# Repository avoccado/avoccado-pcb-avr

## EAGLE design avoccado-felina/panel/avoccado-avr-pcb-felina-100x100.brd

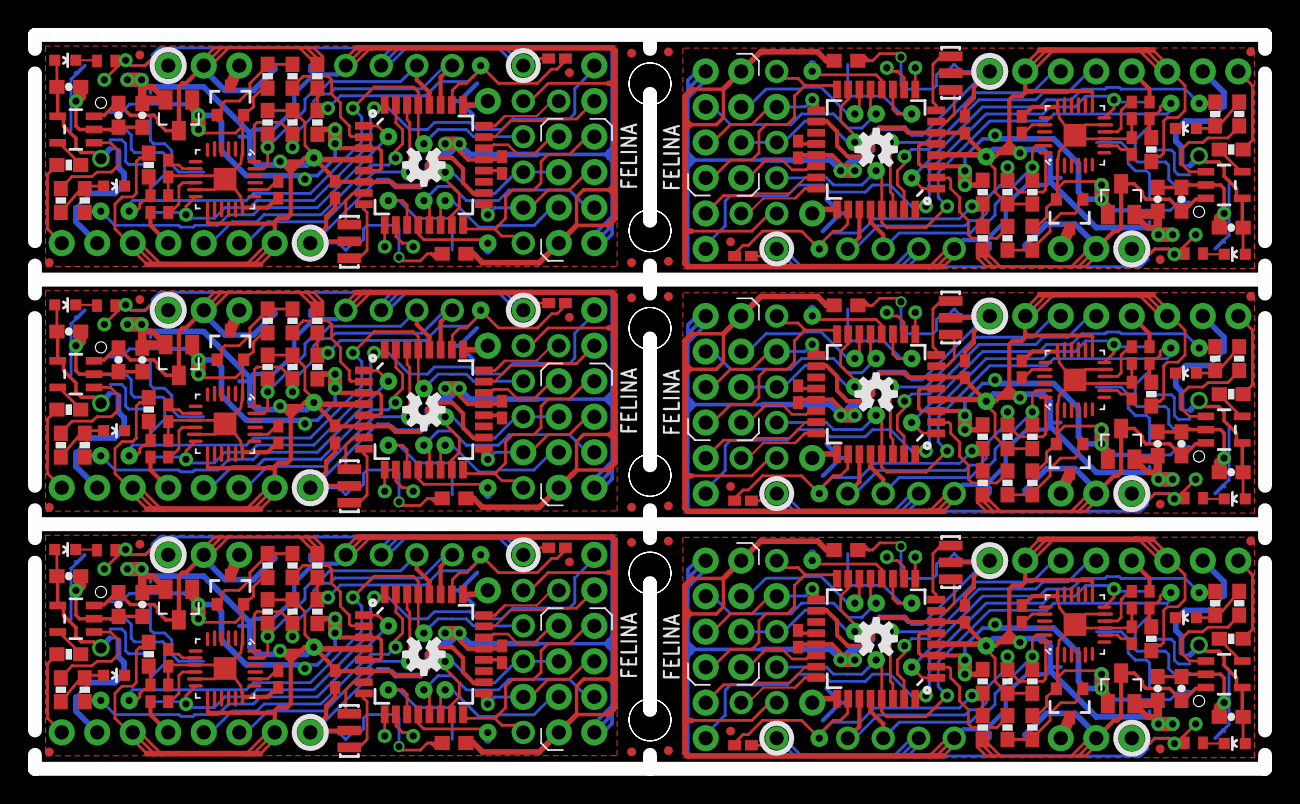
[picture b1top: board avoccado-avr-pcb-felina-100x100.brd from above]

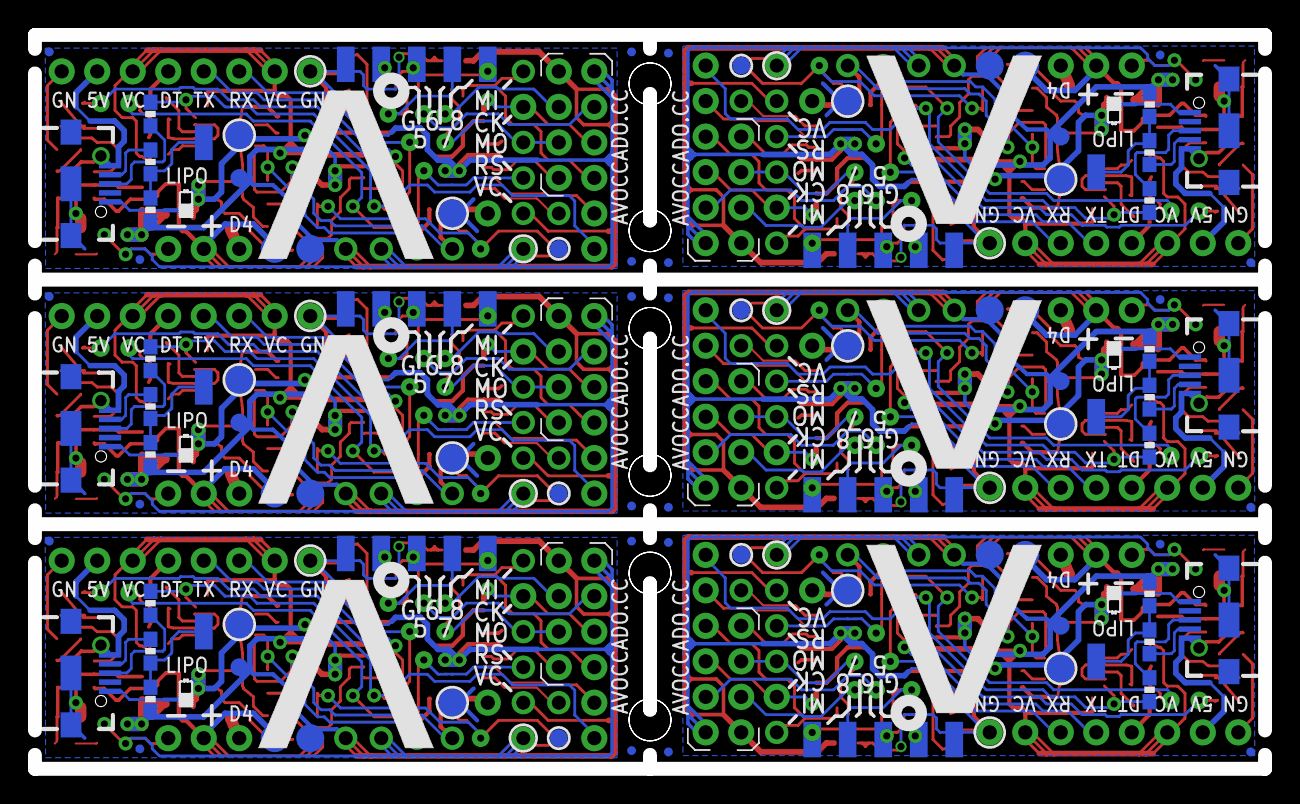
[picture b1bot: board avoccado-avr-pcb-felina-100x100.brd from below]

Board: 2 copper layers, 88.0 x 52.5 mm, 510 parts (120 on the bottom side), 252 nets.

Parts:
C1, C2, C3, C7, C8, C11, C13, C14, C16, C19, C20, C22, C24, C25, C27, C30, C31, C33, C35, C36, C38, C41, C42, C44, C46, C47, C49, C52, C53, C55, C57, C58, C60, C63, C64, C66: 0.1uF; C0402K
C4, C5, C6, C15, C17, C18, C26, C28, C29, C37, C39, C40, C48, C50, C51, C59, C61, C62: 4.7uF; 0603-CAP
C9, C21, C32, C43, C54, C65: 2.2nF; C0402K
C10, C12, C23, C34, C45, C56: 0.1uF; C0603
D1, D2, D3, D4, D5, D6, D7, D8, D9, D10, D11, D12: LED; LED-0603
FID1, FID2, FID3, FID4, FID5, FID6, FID7, FID8, FID9, FID10, FID11, FID12, FID13, FID14, FID15, FID16, FID17, FID18, FID19, FID20, FID21, FID22, FID23, FID24, FID25, FID26, FID27, FID28, FID29, FID30, FID31, FID32, FID33, FID34, FID35, FID36, FID37, FID38, FID39, FID40, FID41, FID42, FID43, FID44, FID45, FID46, FID47, FID48, FID49, FID50, FID51, FID52, FID53, FID54: FIDUCIALUFIDUCIAL; MICRO-FIDUCIAL
JP1, JP4, JP5, JP12, JP14, JP15, JP16, JP20, JP30, JP31, JP35, JP37, JP38, JP43, JP52, JP53, JP54, JP55, JP56, JP57, JP64, JP66, JP67, JP72, JP81, JP82, JP83, JP84, JP85, JP86, JP93, JP95, JP96, JP101, JP110, JP111, JP112, JP113, JP114, JP115, JP122, JP124, JP125, JP130, JP139, JP140, JP141, JP142, JP143, JP144, JP151, JP153, JP154, JP159, JP168, JP169, JP170, JP171, JP172, JP173: M01NOSILK-KIT; 1X01NS-KIT
JP2, JP27, JP28, JP29, JP48, JP49, JP50, JP51, JP77, JP78, JP79, JP80, JP106, JP107, JP108, JP109, JP135, JP136, JP137, JP138, JP164, JP165, JP166, JP167: M021X02_NO_SILK; 1X02_NO_SILK
JP3, JP6, JP7, JP8, JP9, JP10, JP11, JP13, JP17, JP18, JP19, JP21, JP23, JP24, JP25, JP26, JP32, JP33, JP34, JP36, JP39, JP40, JP41, JP42, JP44, JP45, JP46, JP47, JP59, JP60, JP61, JP62, JP63, JP65, JP68, JP69, JP70, JP71, JP73, JP74, JP75, JP76, JP88, JP89, JP90, JP91, JP92, JP94, JP97, JP98, JP99, JP100, JP102, JP103, JP104, JP105, JP117, JP118, JP119, JP120, JP121, JP123, JP126, JP127, JP128, JP129, JP131, JP132, JP133, JP134, JP146, JP147, JP148, JP149, JP150, JP152, JP155, JP156, JP157, JP158, JP160, JP161, JP162, JP163: M01PTH; 1X01
JP22, JP58, JP87, JP116, JP145, JP174: USB_MICROB_PLUGCONN-11752; USB-B-MICRO-SMD_V03
LDO, LDO1, LDO2, LDO3, LDO4, LDO5: MCP1703CB; SOT23
LOGO1, LOGO2, LOGO3, LOGO4, LOGO5, LOGO6: OSHW-LOGOS; OSHW-LOGO-S
MCU, MCU1, MCU2, MCU3, MCU4, MCU5: ATMEGA328P_TQFP; TQFP32-08
Q1, Q3, Q5, Q7, Q9, Q11: 16MHz; RESONATOR-SMD
Q2, Q4, Q6, Q8, Q10, Q12: FET; SOT23-3
R1, R6, R16, R20, R30, R34, R44, R48, R58, R62, R72, R76: 511R; 0603-RES
R2, R10, R11, R12, R23, R24, R29, R37, R38, R43, R51, R52, R57, R65, R66, R71, R79, R80: 10K; 0603-RES
R3, R4, R15, R17, R18, R27, R31, R32, R41, R45, R46, R55, R59, R60, R69, R73, R74, R83: 2K; 0603-RES
R5, R7, R8, R19, R21, R22, R33, R35, R36, R47, R49, R50, R61, R63, R64, R75, R77, R78: 4.7M; 0603-RES
R9, R28, R42, R56, R70, R84: 2K; R0402
R13, R14, R25, R26, R39, R40, R53, R54, R67, R68, R81, R82: 68R; 0603-RES
TP1, TP6, TP7, TP8, TP9, TP11, TP14, TP15, TP16, TP17, TP21, TP23, TP27, TP28, TP29, TP30, TP34, TP36, TP40, TP41, TP42, TP43, TP47, TP49, TP53, TP54, TP55, TP56, TP60, TP62, TP66, TP67, TP68, TP69, TP73, TP75: TEST-POINT2; PAD.02X.02
TP2, TP18, TP31, TP44, TP57, TP70: M01PTH; 1X01
TP3, TP5, TP19, TP20, TP32, TP33, TP45, TP46, TP58, TP59, TP71, TP72: TEST-POINT3X5; PAD.03X.05
TP4, TP10, TP12, TP13, TP22, TP24, TP25, TP26, TP35, TP37, TP38, TP39, TP48, TP50, TP51, TP52, TP61, TP63, TP64, TP65, TP74, TP76, TP77, TP78: TPTP20R; TP20R
U1, U4, U6, U8, U10, U12: MPU-6000QFN-24; QFN-24-TESTING
U2, U3, U5, U7, U9, U11: MCP73831; SOT23-5

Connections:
3.3V1: C12.1, C13.2, C18.1, JP34.1, JP41.1, JP48.2, JP52.1, JP56.1, LDO1.2, MCU1.4, MCU1.6, MCU1.18, R12.2, R23.2, R24.2, R27.2, TP19.P$1, TP25.TP, U4.13
3.3V2: C23.1, C24.2, C29.1, JP63.1, JP70.1, JP77.2, JP81.1, JP85.1, LDO2.2, MCU2.4, MCU2.6, MCU2.18, R29.2, R37.2, R38.2, R41.2, TP32.P$1, TP38.TP, U6.13
3.3V3: C34.1, C35.2, C40.1, JP92.1, JP99.1, JP106.2, JP110.1, JP114.1, LDO3.2, MCU3.4, MCU3.6, MCU3.18, R43.2, R51.2, R52.2, R55.2, TP45.P$1, TP51.TP, U8.13
3.3V4: C45.1, C46.2, C51.1, JP121.1, JP128.1, JP135.2, JP139.1, JP143.1, LDO4.2, MCU4.4, MCU4.6, MCU4.18, R57.2, R65.2, R66.2, R69.2, TP58.P$1, TP64.TP, U10.13
3.3V5: C3.2, C6.1, C10.1, JP1.1, JP2.2, JP4.1, JP11.1, JP18.1, LDO.2, MCU.4, MCU.6, MCU.18, R2.2, R10.2, R11.2, R15.2, TP5.P$1, TP13.TP, U1.13
3.3V6: C56.1, C57.2, C62.1, JP150.1, JP157.1, JP164.2, JP168.1, JP172.1, LDO5.2, MCU5.4, MCU5.6, MCU5.18, R71.2, R79.2, R80.2, R83.2, TP71.P$1, TP77.TP, U12.13
5V1: C15.1, D4.A, JP40.1, JP58.VBUS1, U3.4
5V2: C26.1, D6.A, JP69.1, JP87.VBUS1, U5.4
5V3: C37.1, D8.A, JP98.1, JP116.VBUS1, U7.4
5V4: C48.1, D10.A, JP127.1, JP145.VBUS1, U9.4
5V5: C4.1, D2.A, JP17.1, JP22.VBUS1, U2.4
5V6: C59.1, D12.A, JP156.1, JP174.VBUS1, U11.4
7-TO-D-: R14.1, R15.1, TP11.P$1
7-TO-D-1: R26.1, R27.1, TP23.P$1
7-TO-D-2: R40.1, R41.1, TP36.P$1
7-TO-D-3: R54.1, R55.1, TP49.P$1
7-TO-D-4: R68.1, R69.1, TP62.P$1
7-TO-D-5: R82.1, R83.1, TP75.P$1
A6: JP30.1, MCU.28, R10.1, U1.23
A7: JP54.1, MCU1.28, R23.1, U4.23
A7-NRF-IRQ1: JP51.2, MCU1.22
A7-NRF-IRQ2: JP80.2, MCU2.22
A7-NRF-IRQ3: JP109.2, MCU3.22
A7-NRF-IRQ4: JP138.2, MCU4.22
A7-NRF-IRQ5: JP29.2, MCU.22
A7-NRF-IRQ6: JP167.2, MCU5.22
A8: JP55.1, MCU1.27, R24.1, U4.24
A9: C19.1, MCU1.26, R21.2, R22.1
A10: JP44.1, MCU1.25
A11: JP43.1, MCU1.24
A12: JP42.1, MCU1.23
A14: JP83.1, MCU2.28, R37.1, U6.23
A15: JP84.1, MCU2.27, R38.1, U6.24
A16: C30.1, MCU2.26, R35.2, R36.1
A17: JP73.1, MCU2.25
A18: JP72.1, MCU2.24
A19: JP71.1, MCU2.23
A21: JP112.1, MCU3.28, R51.1, U8.23
A22: JP113.1, MCU3.27, R52.1, U8.24
A23: C41.1, MCU3.26, R49.2, R50.1
A24: JP102.1, MCU3.25
A25: JP101.1, MCU3.24
A26: JP100.1, MCU3.23
A28: JP141.1, MCU4.28, R65.1, U10.23
A29: JP142.1, MCU4.27, R66.1, U10.24
A30: C52.1, MCU4.26, R63.2, R64.1
A31: JP131.1, MCU4.25
A32: JP130.1, MCU4.24
A33: JP129.1, MCU4.23
A35: JP31.1, MCU.27, R11.1, U1.24
A36: C7.1, MCU.26, R7.2, R8.1
A37: JP21.1, MCU.25
A38: JP20.1, MCU.24
A39: JP19.1, MCU.23
A41: JP170.1, MCU5.28, R79.1, U12.23
A42: JP171.1, MCU5.27, R80.1, U12.24
A43: C63.1, MCU5.26, R77.2, R78.1
A44: JP160.1, MCU5.25
A45: JP159.1, MCU5.24
A46: JP158.1, MCU5.23
AREF1: C14.2, MCU1.20
AREF2: C25.2, MCU2.20
AREF3: C36.2, MCU3.20
AREF4: C47.2, MCU4.20
AREF5: C1.2, MCU.20
AREF6: C58.2, MCU5.20
CHG-PROG1: R17.2, U3.5
CHG-PROG2: R31.2, U5.5
CHG-PROG3: R45.2, U7.5
CHG-PROG4: R59.2, U9.5
CHG-PROG5: R3.2, U2.5
CHG-PROG6: R73.2, U11.5
D1: JP49.1, MCU1.13
D2: MCU1.12, TP17.P$1
D2-INT1: MCU1.32, R25.1, TP18.1, U4.12
D2-INT2: MCU2.32, R39.1, TP31.1, U6.12
D2-INT3: MCU3.32, R53.1, TP44.1, U8.12
D2-INT4: MCU4.32, R67.1, TP57.1, U10.12
D2-INT5: MCU.32, R13.1, TP2.1, U1.12
D2-INT6: MCU5.32, R81.1, TP70.1, U12.12
D3: JP27.1, MCU.13
D8: MCU.12, TP8.P$1
D11: MCU1.1, R20.1
D12: MCU1.2, R16.1
D13: MCU1.9, TP14.P$1
D14: MCU1.10, TP15.P$1
D15: MCU1.11, TP16.P$1
D16: JP49.2, MCU1.14
D17: JP78.1, MCU2.13
D18: MCU2.12, TP30.P$1
D19: MCU2.1, R34.1
D20: MCU2.2, R30.1
D21: MCU2.9, TP27.P$1
D22: MCU2.10, TP28.P$1
D23: MCU2.11, TP29.P$1
D24: JP78.2, MCU2.14
D25: JP107.1, MCU3.13
D26: MCU3.12, TP43.P$1
D27: MCU3.1, R48.1
D28: MCU3.2, R44.1
D29: MCU3.9, TP40.P$1
D30: MCU3.10, TP41.P$1
D31: MCU3.11, TP42.P$1
D32: JP107.2, MCU3.14
D33: JP136.1, MCU4.13
D34: MCU4.12, TP56.P$1
D35: MCU4.1, R62.1
D36: MCU4.2, R58.1
D37: MCU4.9, TP53.P$1
D38: MCU4.10, TP54.P$1
D39: MCU4.11, TP55.P$1
D40: JP136.2, MCU4.14
D41: MCU.1, R6.1
D42: MCU.2, R1.1
D43: MCU.9, TP1.P$1
D44: MCU.10, TP6.P$1
D45: MCU.11, TP7.P$1
D46: JP27.2, MCU.14
D47: JP165.1, MCU5.13
D48: MCU5.12, TP69.P$1
D49: MCU5.1, R76.1
D50: MCU5.2, R72.1
D51: MCU5.9, TP66.P$1
D52: MCU5.10, TP67.P$1
D53: MCU5.11, TP68.P$1
D54: JP165.2, MCU5.14
DTR1: C16.2, JP33.1
DTR2: C27.2, JP62.1
DTR3: C38.2, JP91.1
DTR4: C49.2, JP120.1
DTR5: C2.2, JP10.1
DTR6: C60.2, JP149.1
GND: C1.1, C3.1, C4.2, C5.2, C6.2, C7.2, C8.2, C9.2, C10.2, C11.2, D1.C, JP2.1, JP3.1, JP5.1, JP6.1, JP16.1, JP22.GND1, JP22.SHIELD1, JP22.SHIELD2, JP22.SHIELD3, JP25.1, LDO.1, MCU.3, MCU.5, MCU.21, Q1.2, Q2.2, R3.1, R5.1, R7.1, R9.1, TP3.P$1, TP4.TP, TP9.P$1, TP12.TP, U1.1, U1.9, U1.11, U1.18, U2.2
GND1: C12.2, C13.1, C14.1, C15.2, C17.2, C18.2, C19.2, C20.2, C21.2, C22.2, D3.C, JP7.1, JP39.1, JP47.1, JP48.1, JP53.1, JP57.1, JP58.GND1, JP58.SHIELD1, JP58.SHIELD2, JP58.SHIELD3, LDO1.1, MCU1.3, MCU1.5, MCU1.21, Q3.2, Q4.2, R17.1, R19.1, R21.1, R28.1, TP20.P$1, TP21.P$1, TP24.TP, TP26.TP, U3.2, U4.1, U4.9, U4.11, U4.18
GND2: C23.2, C24.1, C25.1, C26.2, C28.2, C29.2, C30.2, C31.2, C32.2, C33.2, D5.C, JP59.1, JP68.1, JP76.1, JP77.1, JP82.1, JP86.1, JP87.GND1, JP87.SHIELD1, JP87.SHIELD2, JP87.SHIELD3, LDO2.1, MCU2.3, MCU2.5, MCU2.21, Q5.2, Q6.2, R31.1, R33.1, R35.1, R42.1, TP33.P$1, TP34.P$1, TP37.TP, TP39.TP, U5.2, U6.1, U6.9, U6.11, U6.18
GND3: C34.2, C35.1, C36.1, C37.2, C39.2, C40.2, C41.2, C42.2, C43.2, C44.2, D7.C, JP88.1, JP97.1, JP105.1, JP106.1, JP111.1, JP115.1, JP116.GND1, JP116.SHIELD1, JP116.SHIELD2, JP116.SHIELD3, LDO3.1, MCU3.3, MCU3.5, MCU3.21, Q7.2, Q8.2, R45.1, R47.1, R49.1, R56.1, TP46.P$1, TP47.P$1, TP50.TP, TP52.TP, U7.2, U8.1, U8.9, U8.11, U8.18
GND4: C45.2, C46.1, C47.1, C48.2, C50.2, C51.2, C52.2, C53.2, C54.2, C55.2, D9.C, JP117.1, JP126.1, JP134.1, JP135.1, JP140.1, JP144.1, JP145.GND1, JP145.SHIELD1, JP145.SHIELD2, JP145.SHIELD3, LDO4.1, MCU4.3, MCU4.5, MCU4.21, Q9.2, Q10.2, R59.1, R61.1, R63.1, R70.1, TP59.P$1, TP60.P$1, TP63.TP, TP65.TP, U9.2, U10.1, U10.9, U10.11, U10.18
GND5: C56.2, C57.1, C58.1, C59.2, C61.2, C62.2, C63.2, C64.2, C65.2, C66.2, D11.C, JP146.1, JP155.1, JP163.1, JP164.1, JP169.1, JP173.1, JP174.GND1, JP174.SHIELD1, JP174.SHIELD2, JP174.SHIELD3, LDO5.1, MCU5.3, MCU5.5, MCU5.21, Q11.2, Q12.2, R73.1, R75.1, R77.1, R84.1, TP72.P$1, TP73.P$1, TP76.TP, TP78.TP, U11.2, U12.1, U12.9, U12.11, U12.18
LED1: D3.A, R18.1, R20.2
LED2: D5.A, R32.1, R34.2
LED3: D7.A, R46.1, R48.2
LED4: D9.A, R60.1, R62.2
LED5: D1.A, R4.1, R6.2
LED6: D11.A, R74.1, R76.2
MISO1: JP35.1, JP51.1, MCU1.16
MISO2: JP64.1, JP80.1, MCU2.16
MISO3: JP93.1, JP109.1, MCU3.16
MISO4: JP122.1, JP138.1, MCU4.16
MISO5: JP12.1, JP29.1, MCU.16
MISO6: JP151.1, JP167.1, MCU5.16
MOSI1: JP37.1, JP50.2, MCU1.15
MOSI2: JP66.1, JP79.2, MCU2.15
MOSI3: JP95.1, JP108.2, MCU3.15
MOSI4: JP124.1, JP137.2, MCU4.15
MOSI5: JP14.1, JP28.2, MCU.15
MOSI6: JP153.1, JP166.2, MCU5.15
unnamed: MCU.8, Q1.1
unnamed: MCU.7, Q1.3
unnamed: Q2.1, R1.2, R5.2
unnamed: MCU1.8, Q3.1
unnamed: MCU1.7, Q3.3
unnamed: Q4.1, R16.2, R19.2
unnamed: C20.1, U4.10
unnamed: C21.1, U4.20
unnamed: C22.1, U4.8
unnamed: JP58.D+1, R25.2
unnamed: JP58.D-1, R26.2
unnamed: D4.C, R28.2
unnamed: MCU2.8, Q5.1
unnamed: MCU2.7, Q5.3
unnamed: Q6.1, R30.2, R33.2
unnamed: C31.1, U6.10
unnamed: C32.1, U6.20
unnamed: C33.1, U6.8
unnamed: JP87.D+1, R39.2
unnamed: JP87.D-1, R40.2
unnamed: D6.C, R42.2
unnamed: MCU3.8, Q7.1
unnamed: MCU3.7, Q7.3
unnamed: Q8.1, R44.2, R47.2
unnamed: C42.1, U8.10
unnamed: C43.1, U8.20
unnamed: C44.1, U8.8
unnamed: JP116.D+1, R53.2
unnamed: JP116.D-1, R54.2
unnamed: D8.C, R56.2
unnamed: MCU4.8, Q9.1
unnamed: MCU4.7, Q9.3
unnamed: Q10.1, R58.2, R61.2
unnamed: C53.1, U10.10
unnamed: C54.1, U10.20
unnamed: C55.1, U10.8
unnamed: JP145.D+1, R67.2
unnamed: JP145.D-1, R68.2
unnamed: D10.C, R70.2
unnamed: C8.1, U1.10
unnamed: C9.1, U1.20
unnamed: C11.1, U1.8
unnamed: JP22.D+1, R13.2
unnamed: JP22.D-1, R14.2
unnamed: D2.C, R9.2
unnamed: MCU5.8, Q11.1
unnamed: MCU5.7, Q11.3
unnamed: Q12.1, R72.2, R75.2
unnamed: C64.1, U12.10
unnamed: C65.1, U12.20
unnamed: C66.1, U12.8
unnamed: JP174.D+1, R81.2
unnamed: JP174.D-1, R82.2
unnamed: D12.C, R84.2
RESET1: C16.1, JP38.1, MCU1.29, R12.1
RESET2: C27.1, JP67.1, MCU2.29, R29.1
RESET3: C38.1, JP96.1, MCU3.29, R43.1
RESET4: C49.1, JP125.1, MCU4.29, R57.1
RESET5: C2.1, JP15.1, MCU.29, R2.1
RESET6: C60.1, JP154.1, MCU5.29, R71.1
RXI1: JP26.1, MCU1.30
RXI2: JP60.1, MCU2.30
RXI3: JP89.1, MCU3.30
RXI4: JP118.1, MCU4.30
RXI5: JP8.1, MCU.30
RXI6: JP147.1, MCU5.30
SCK1: JP36.1, JP50.1, MCU1.17
SCK2: JP65.1, JP79.1, MCU2.17
SCK3: JP94.1, JP108.1, MCU3.17
SCK4: JP123.1, JP137.1, MCU4.17
SCK5: JP13.1, JP28.1, MCU.17
SCK6: JP152.1, JP166.1, MCU5.17
SOC: R4.2, U2.1
SOC1: R18.2, U3.1
SOC2: R32.2, U5.1
SOC3: R46.2, U7.1
SOC4: R60.2, U9.1
SOC5: R74.2, U11.1
TXO1: JP32.1, MCU1.31
TXO2: JP61.1, MCU2.31
TXO3: JP90.1, MCU3.31
TXO4: JP119.1, MCU4.31
TXO5: JP9.1, MCU.31
TXO6: JP148.1, MCU5.31
VBAT1: C17.1, JP45.1, LDO1.3, R22.2, TP22.TP, U3.3
VBAT2: C28.1, JP74.1, LDO2.3, R36.2, TP35.TP, U5.3
VBAT3: C39.1, JP103.1, LDO3.3, R50.2, TP48.TP, U7.3
VBAT4: C50.1, JP132.1, LDO4.3, R64.2, TP61.TP, U9.3
VBAT5: C5.1, JP24.1, LDO.3, R8.2, TP10.TP, U2.3
VBAT6: C61.1, JP161.1, LDO5.3, R78.2, TP74.TP, U11.3
VIBR1: JP46.1, Q4.3
VIBR2: JP75.1, Q6.3
VIBR3: JP104.1, Q8.3
VIBR4: JP133.1, Q10.3
VIBR5: JP23.1, Q2.3
VIBR6: JP162.1, Q12.3

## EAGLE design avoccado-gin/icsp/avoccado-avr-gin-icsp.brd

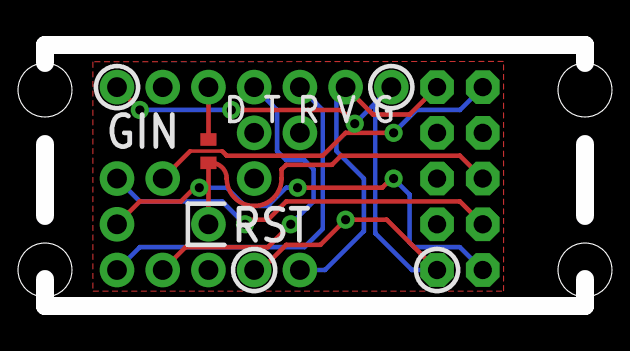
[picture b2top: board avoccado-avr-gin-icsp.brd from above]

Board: 2 copper layers, 30.0 x 14.5 mm, 21 parts (1 on the bottom side), 9 nets.

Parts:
C1: C0402
TP1, TP3, TP4, TP5, TP8, TP13, TP17, TP18, TP19, TP20, TP21, TP22, TP23, TP24, TP25, TP26, TP28, TP29, TP30: PTR1PAD1-13; P1-13
U$1: AVR_SPI_PROG; AVR_ICSP

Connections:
3.3V: TP8.TP, TP22.TP, TP28.TP, U$1.2
DTR: C1.2, TP1.TP
GND: TP18.TP, TP24.TP, TP29.TP, U$1.10
MISO: TP21.TP, U$1.9
MOSI: TP19.TP, U$1.1
RESET: C1.1, TP23.TP, U$1.5
RXI: TP3.TP, TP25.TP
SCK: TP20.TP, U$1.7
TXO: TP5.TP, TP26.TP

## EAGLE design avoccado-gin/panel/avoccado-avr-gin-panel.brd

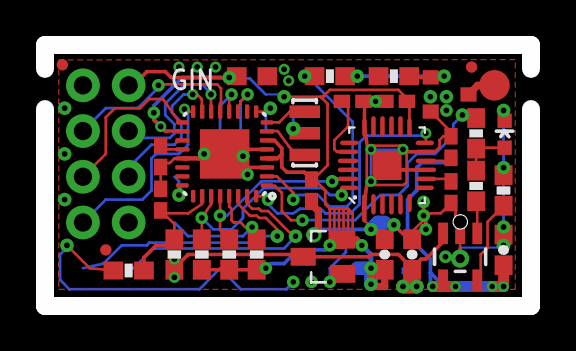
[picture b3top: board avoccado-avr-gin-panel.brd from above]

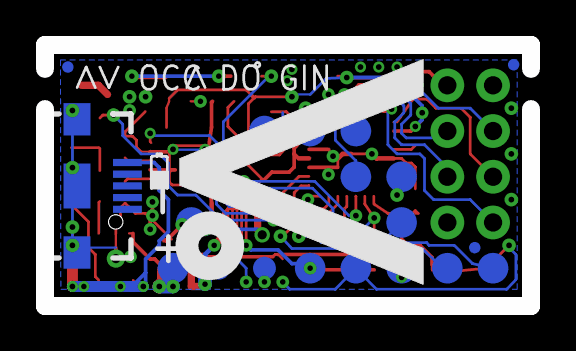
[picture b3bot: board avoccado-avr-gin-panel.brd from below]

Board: 2 copper layers, 27.0 x 14.5 mm, 55 parts (19 on the bottom side), 33 nets.

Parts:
C1, C2, C3, C7, C8, C11: 0.1uF; C0402K
C4, C5, C6: 4.7uF; 0603-CAP
C9: 2.2nF; C0402K
C10: 4.7uF; C0603
D1: LED; LED-0603
FID2, FID4, FID5, FID6, FID8, FID9: FIDUCIALUFIDUCIAL; MICRO-FIDUCIAL
JP2, JP27, JP28, JP29: M021X02_NO_SILK; 1X02_NO_SILK
JP22: USB_MICROB_PLUGCONN-11752; USB-B-MICRO-SMD_V03
LDO: MCP1703CB; SOT23
Q1: 16MHz; RESONATOR-SMD
Q2: N-FET; SOT23-3
R1, R6: 511R; 0603-RES
R2, R10, R11: 10K; 0603-RES
R3, R4: 2K; 0603-RES
R5, R7, R8: 4.7M; 0603-RES
TP1, TP2, TP4, TP6, TP7, TP8, TP9, TP10, TP11, TP12, TP14, TP15, TP16, TP17: TPTP20R; TP20R
TP3, TP5: TEST-POINT3X5; PAD.03X.05
U1: MPU-6000QFN-24; QFN-24-TESTING
U2: MCP73831; SOT23-5
U3: MLF32-PAD

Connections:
3.3V: C2.2, C3.2, C6.1, C10.1, JP2.2, LDO.2, R2.2, R10.2, R11.2, TP5.P$1, TP9.TP, U1.13, U3.4, U3.6, U3.18
5V: C4.1, JP22.VBUS1, U2.4
A1: TP8.TP, U3.24
A3: C7.1, R7.2, R8.1, U3.26
A4: R11.1, U1.24, U3.27
A5: R10.1, U1.23, U3.28
AREF: C1.2, U3.20
CHG-PROG: R3.2, U2.5
D2-INT: U1.12, U3.32
D3: R6.1, U3.1
D4: R1.1, U3.2
D5: TP15.TP, U3.9
D7: TP14.TP, U3.11
D8: TP11.TP, U3.12
D9: JP27.1, U3.13
D10: JP27.2, U3.14
GND: C1.1, C2.1, C3.1, C4.2, C5.2, C6.2, C7.2, C8.2, C9.2, C10.2, C11.2, D1.C, JP2.1, JP22.GND1, JP22.SHIELD1, JP22.SHIELD2, JP22.SHIELD3, LDO.1, Q1.2, Q2.2, R3.1, R5.1, R7.1, TP3.P$1, TP12.TP, TP16.TP, TP17.TP, U1.1, U1.9, U1.11, U1.18, U2.2, U3.3, U3.5, U3.21, U3.PAD
LED: D1.A, R4.1, R6.2
MISO: JP29.1, U3.16
MOSI: JP28.2, U3.15
unnamed: Q1.1, U3.8
unnamed: Q1.3, U3.7
unnamed: Q2.1, R1.2, R5.2
unnamed: C8.1, U1.10
unnamed: C9.1, U1.20
unnamed: C11.1, U1.8
RESET: R2.1, TP7.TP, U3.29
RXI: TP2.TP, U3.30
SCK: JP28.1, U3.17
SOC: R4.2, U2.1
TXO: TP6.TP, U3.31
VBAT: C5.1, LDO.3, R8.2, TP4.TP, TP10.TP, U2.3
VIBR: Q2.3, TP1.TP

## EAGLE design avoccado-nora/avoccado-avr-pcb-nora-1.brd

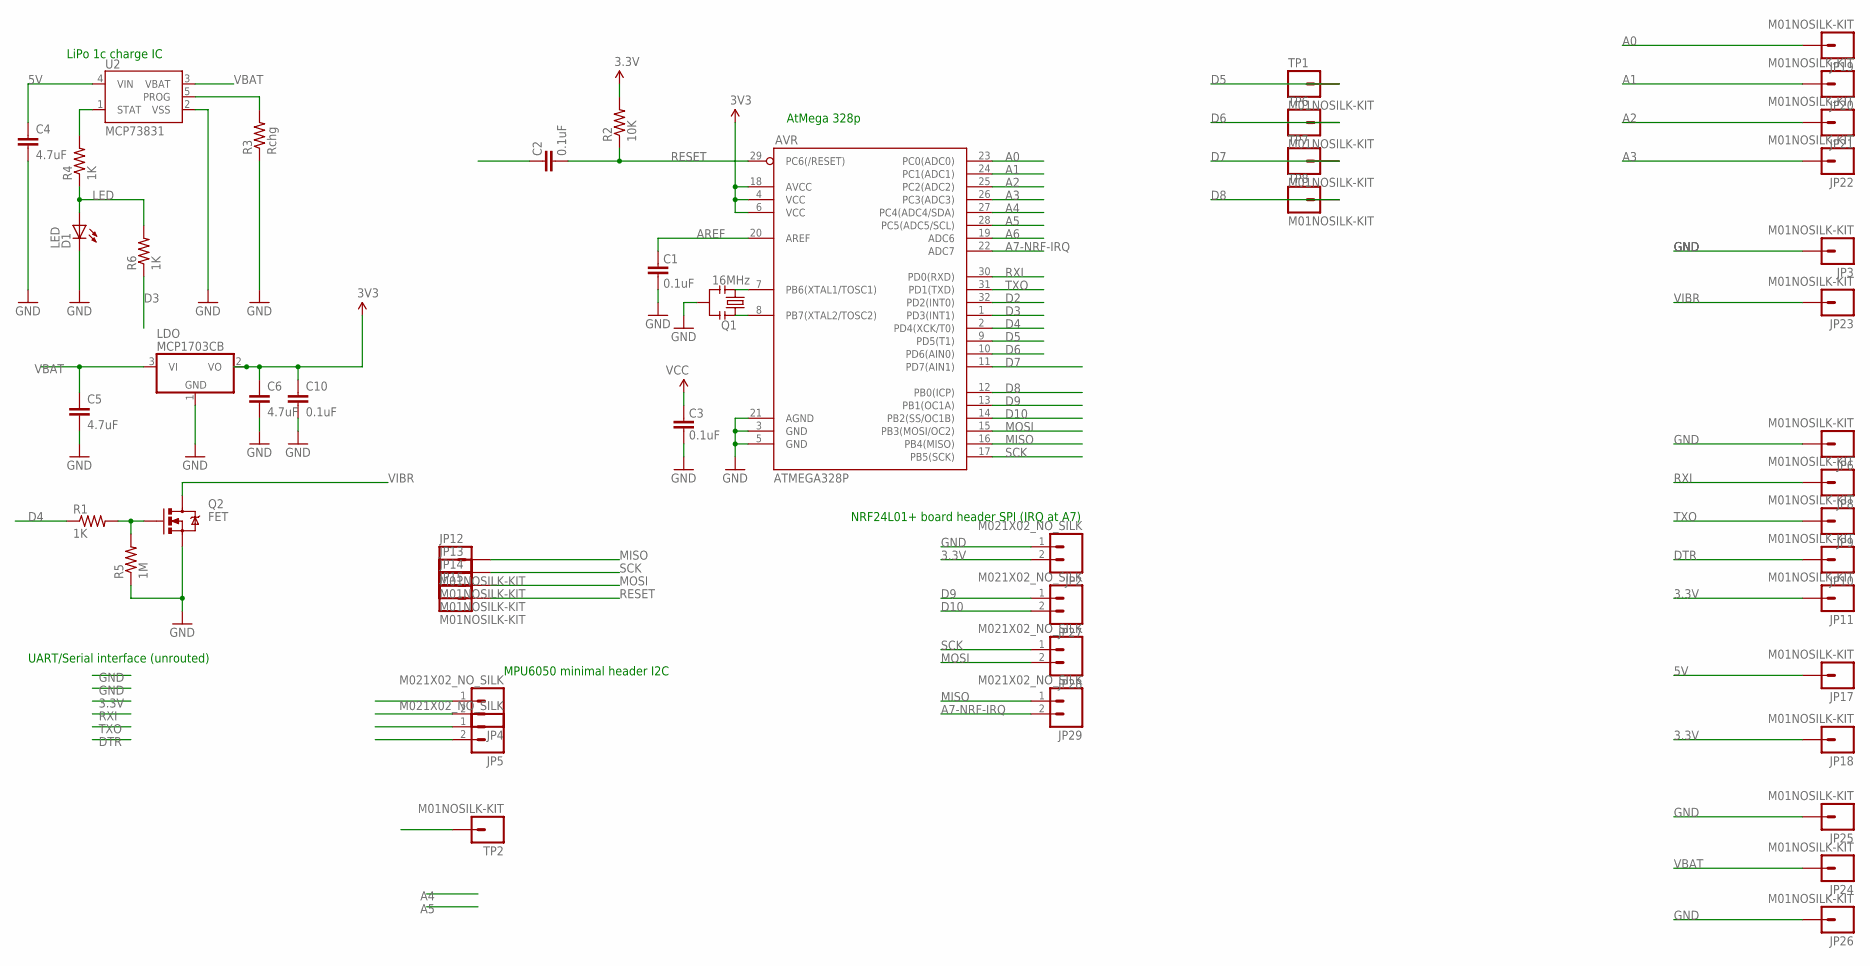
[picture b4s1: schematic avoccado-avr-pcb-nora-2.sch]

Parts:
AVR: ATMEGA328P; TQFP32-08
C1, C2, C3, C10: 0.1uF; C0402
C4, C5, C6: 4.7uF; 0603-CAP
D1: LED; LED-0603
JP2, JP4, JP5, JP27, JP28, JP29: M021X02_NO_SILK; 1X02_NO_SILK
JP3, JP6, JP8, JP9, JP10, JP11, JP12, JP13, JP14, JP15, JP17, JP18, JP19, JP20, JP21, JP22, JP23, JP24, JP25, JP26: M01NOSILK-KIT; 1X01NS-KIT
LDO: MCP1703CB; SOT23
Q1: 16MHz; RESONATOR-SMD
Q2: FET; SOT323
R1, R4, R6: 1K; 0603-RES
R2: 10K; 0603-RES
R3: Rchg; 0603-RES
R5: 1M; 0603-RES
TP1, TP2, TP6, TP7, TP8: M01NOSILK-KIT; 1X01NS-KIT
U2: MCP73831; SOT23-5

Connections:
3.3V: AVR.4 (VCC), AVR.6 (VCC), AVR.18 (AVCC), C3.2, C6.1, C10.1, JP2.2, JP4.1, JP11.1, JP18.1, LDO.2 (VO), R2.2
5V: C4.1, JP17.1, U2.4 (VIN)
A0: AVR.23 (PC0(ADC0)), JP19.1
A1: AVR.24 (PC1(ADC1)), JP20.1
A2: AVR.25 (PC2(ADC2)), JP21.1
A3: AVR.26 (PC3(ADC3)), JP22.1
A4: AVR.27 (PC4(ADC4/SDA)), JP5.2
A5: AVR.28 (PC5(ADC5/SCL)), JP5.1
A6: AVR.19 (ADC6)
A7-NRF-IRQ: AVR.22 (ADC7), JP29.2
AREF: AVR.20 (AREF), C1.2
CHG-PROG: R3.2, U2.5 (PROG)
D2: AVR.32 (PD2(INT0)), TP2.1
D3: AVR.1 (PD3(INT1)), R6.1
D4: AVR.2 (PD4(XCK/T0)), R1.1
D5: AVR.9 (PD5(T1)), TP1.1
D6: AVR.10 (PD6(AIN0)), TP6.1
D7: AVR.11 (PD7(AIN1)), TP7.1
D8: AVR.12 (PB0(ICP)), TP8.1
D9: AVR.13 (PB1(OC1A)), JP27.1
D10: AVR.14 (PB2(SS/OC1B)), JP27.2
DTR: C2.2, JP10.1
GND: AVR.3 (GND), AVR.5 (GND), AVR.21 (AGND), C1.1, C3.1, C4.2, C5.2, C6.2, C10.2, D1.C, JP2.1, JP3.1, JP4.2, JP6.1, JP25.1, JP26.1, LDO.1 (GND), Q1.2, Q2.2 (S), R3.1, R5.1, U2.2 (VSS)
LED: D1.A, R4.1, R6.2
MISO: AVR.16 (PB4(MISO)), JP12.1, JP29.1
MOSI: AVR.15 (PB3(MOSI/OC2)), JP14.1, JP28.2
unnamed: AVR.8 (PB7(XTAL2/TOSC2)), Q1.1
unnamed: AVR.7 (PB6(XTAL1/TOSC1)), Q1.3
unnamed: Q2.1 (G), R1.2, R5.2
RESET: AVR.29 (PC6(/RESET)), C2.1, JP15.1, R2.1
RXI: AVR.30 (PD0(RXD)), JP8.1
SCK: AVR.17 (PB5(SCK)), JP13.1, JP28.1
SOC: R4.2, U2.1 (STAT)
TXO: AVR.31 (PD1(TXD)), JP9.1
VBAT: C5.1, JP24.1, LDO.3 (VI), U2.3 (VBAT)
VIBR: JP23.1, Q2.3 (D)

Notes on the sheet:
NRF24L01+ board header SPI (IRQ at A7)
MPU6050 minimal header I2C
AtMega 328p
LiPo 1c charge IC
UART/Serial interface (unrouted)

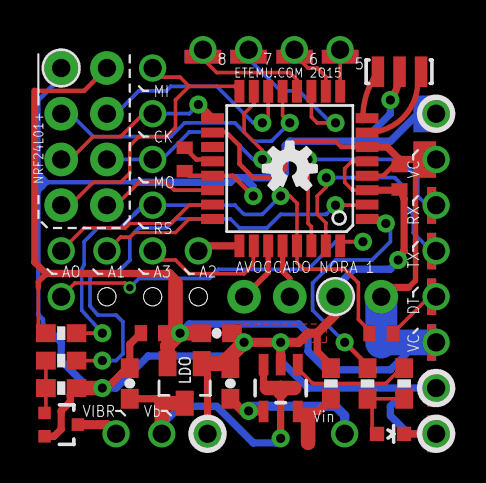
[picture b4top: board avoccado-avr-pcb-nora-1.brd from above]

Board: 2 copper layers, 52 parts (1 on the bottom side), 34 nets.

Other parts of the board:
LOGO1, LOGO2: OSHW-LOGOS; OSHW-LOGO-S

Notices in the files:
parts and their libraries:
SparkFun-DiscreteSemi: Licensing: Creative Commons ShareAlike 4.0 International - https://creativecommons.org/licenses/by-sa/4.0
